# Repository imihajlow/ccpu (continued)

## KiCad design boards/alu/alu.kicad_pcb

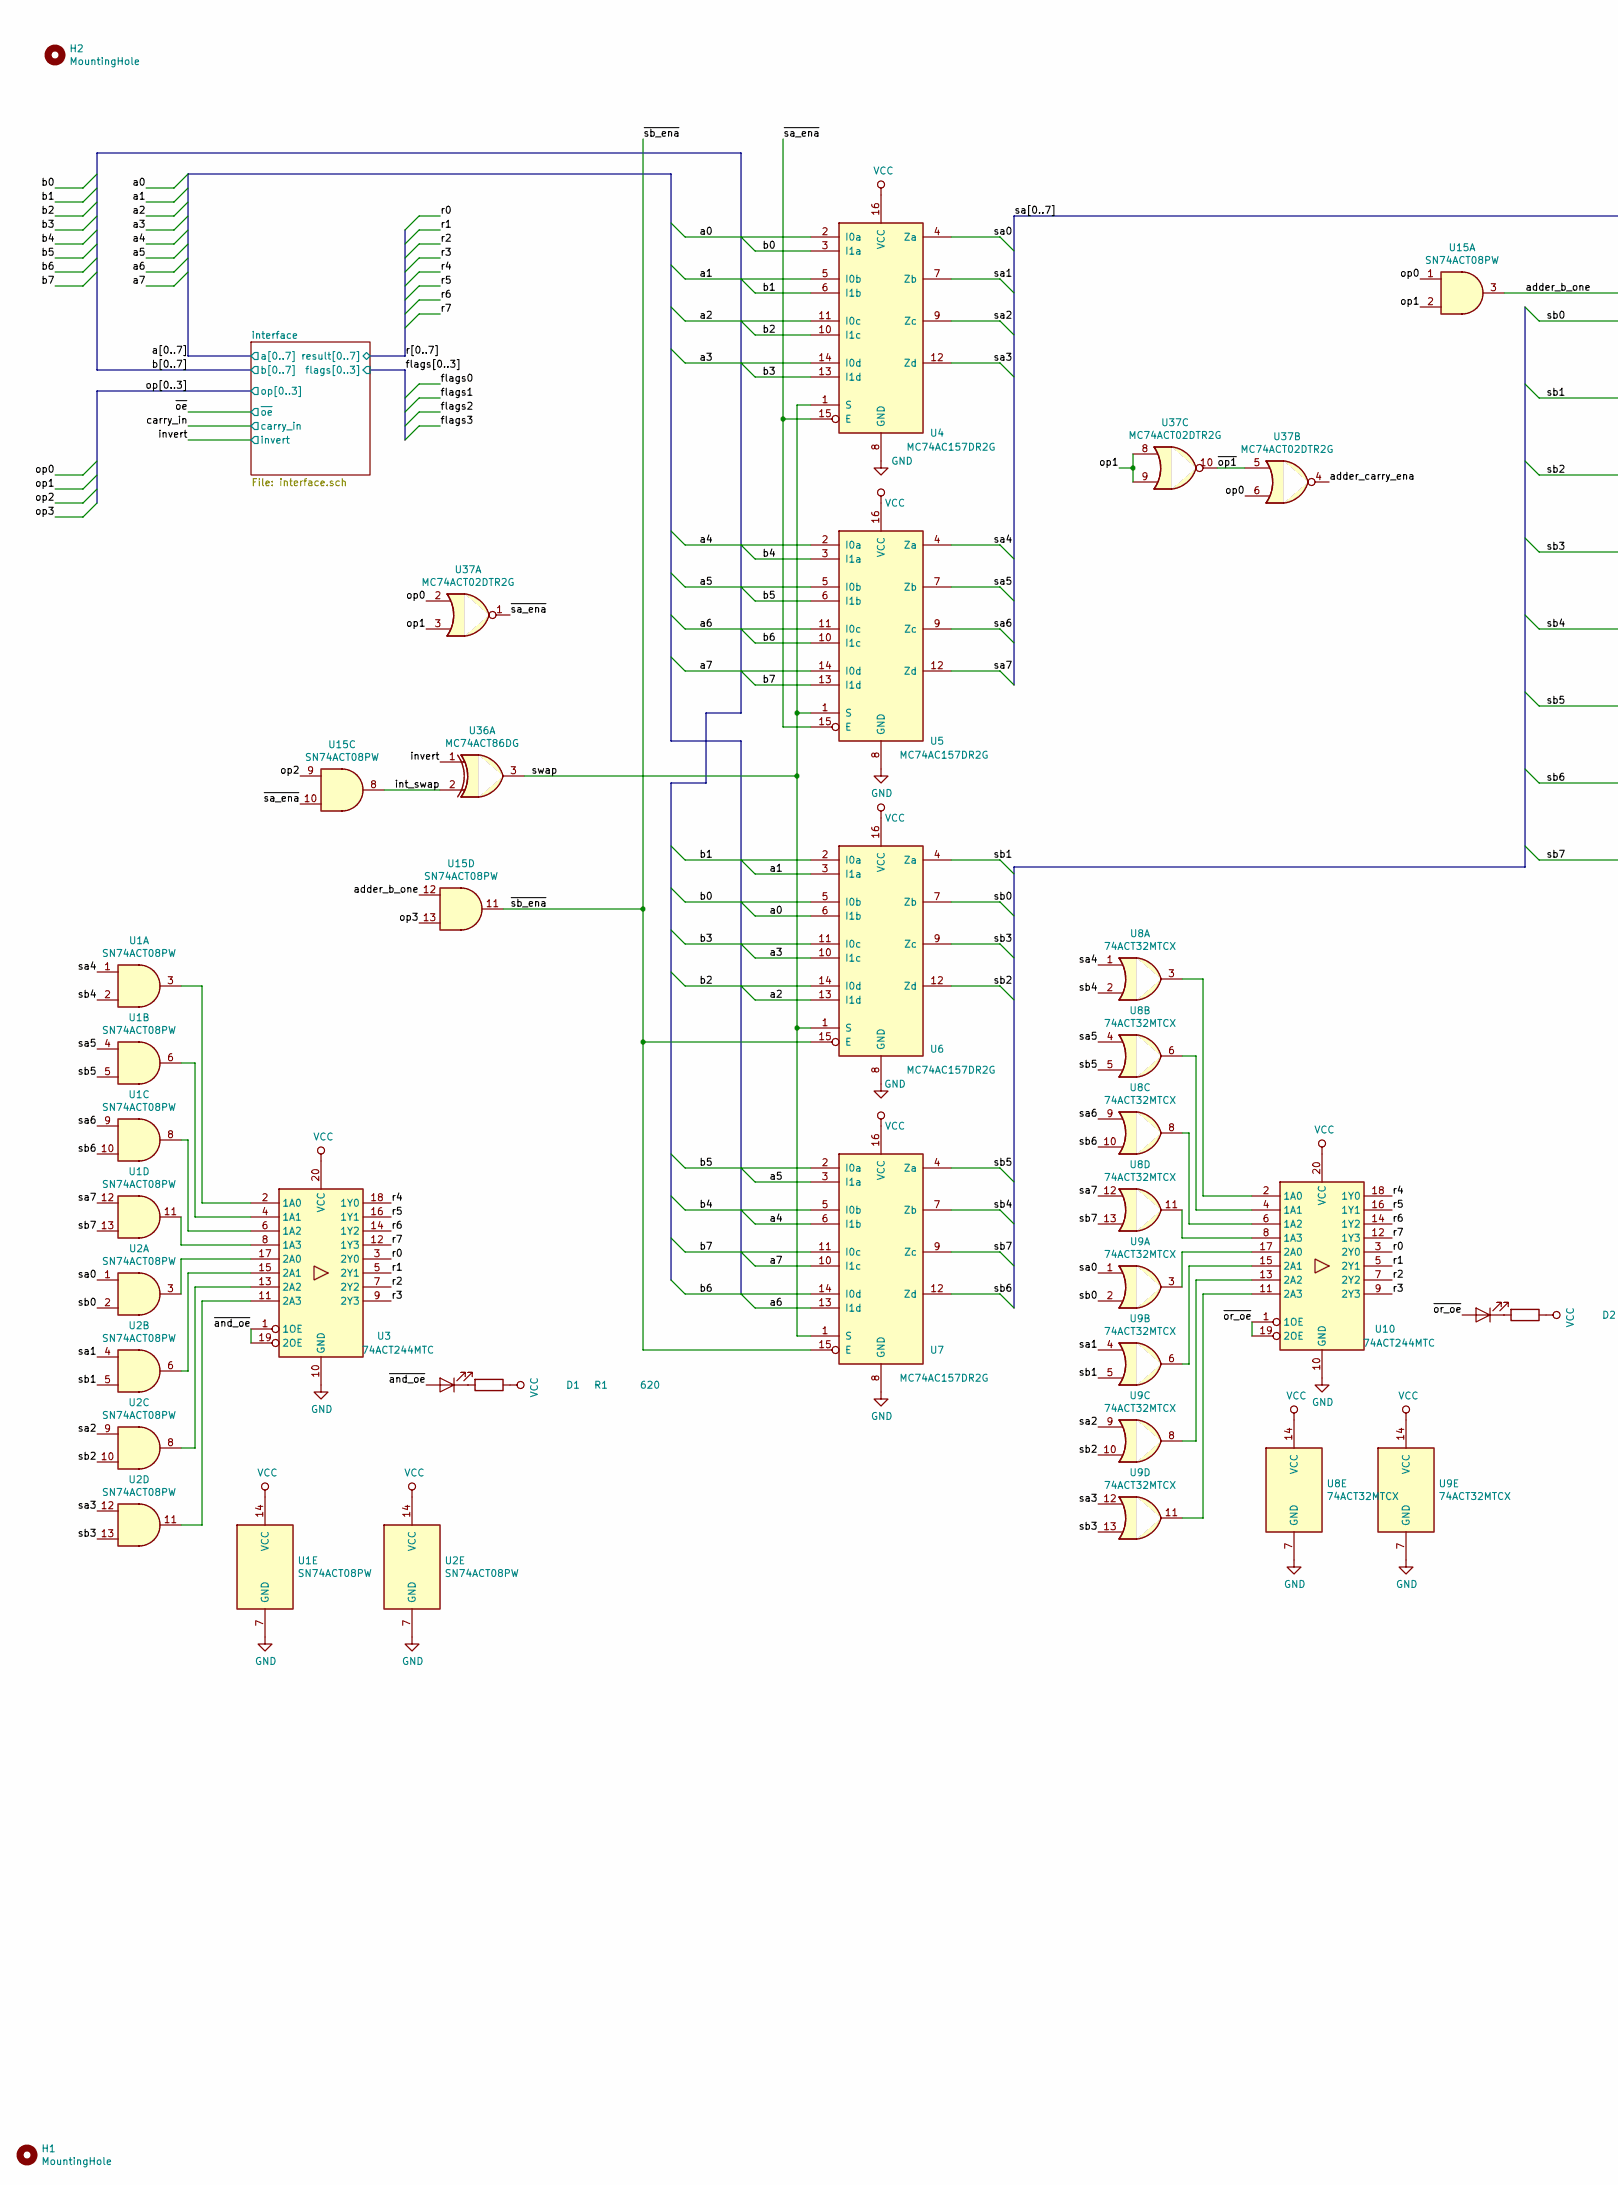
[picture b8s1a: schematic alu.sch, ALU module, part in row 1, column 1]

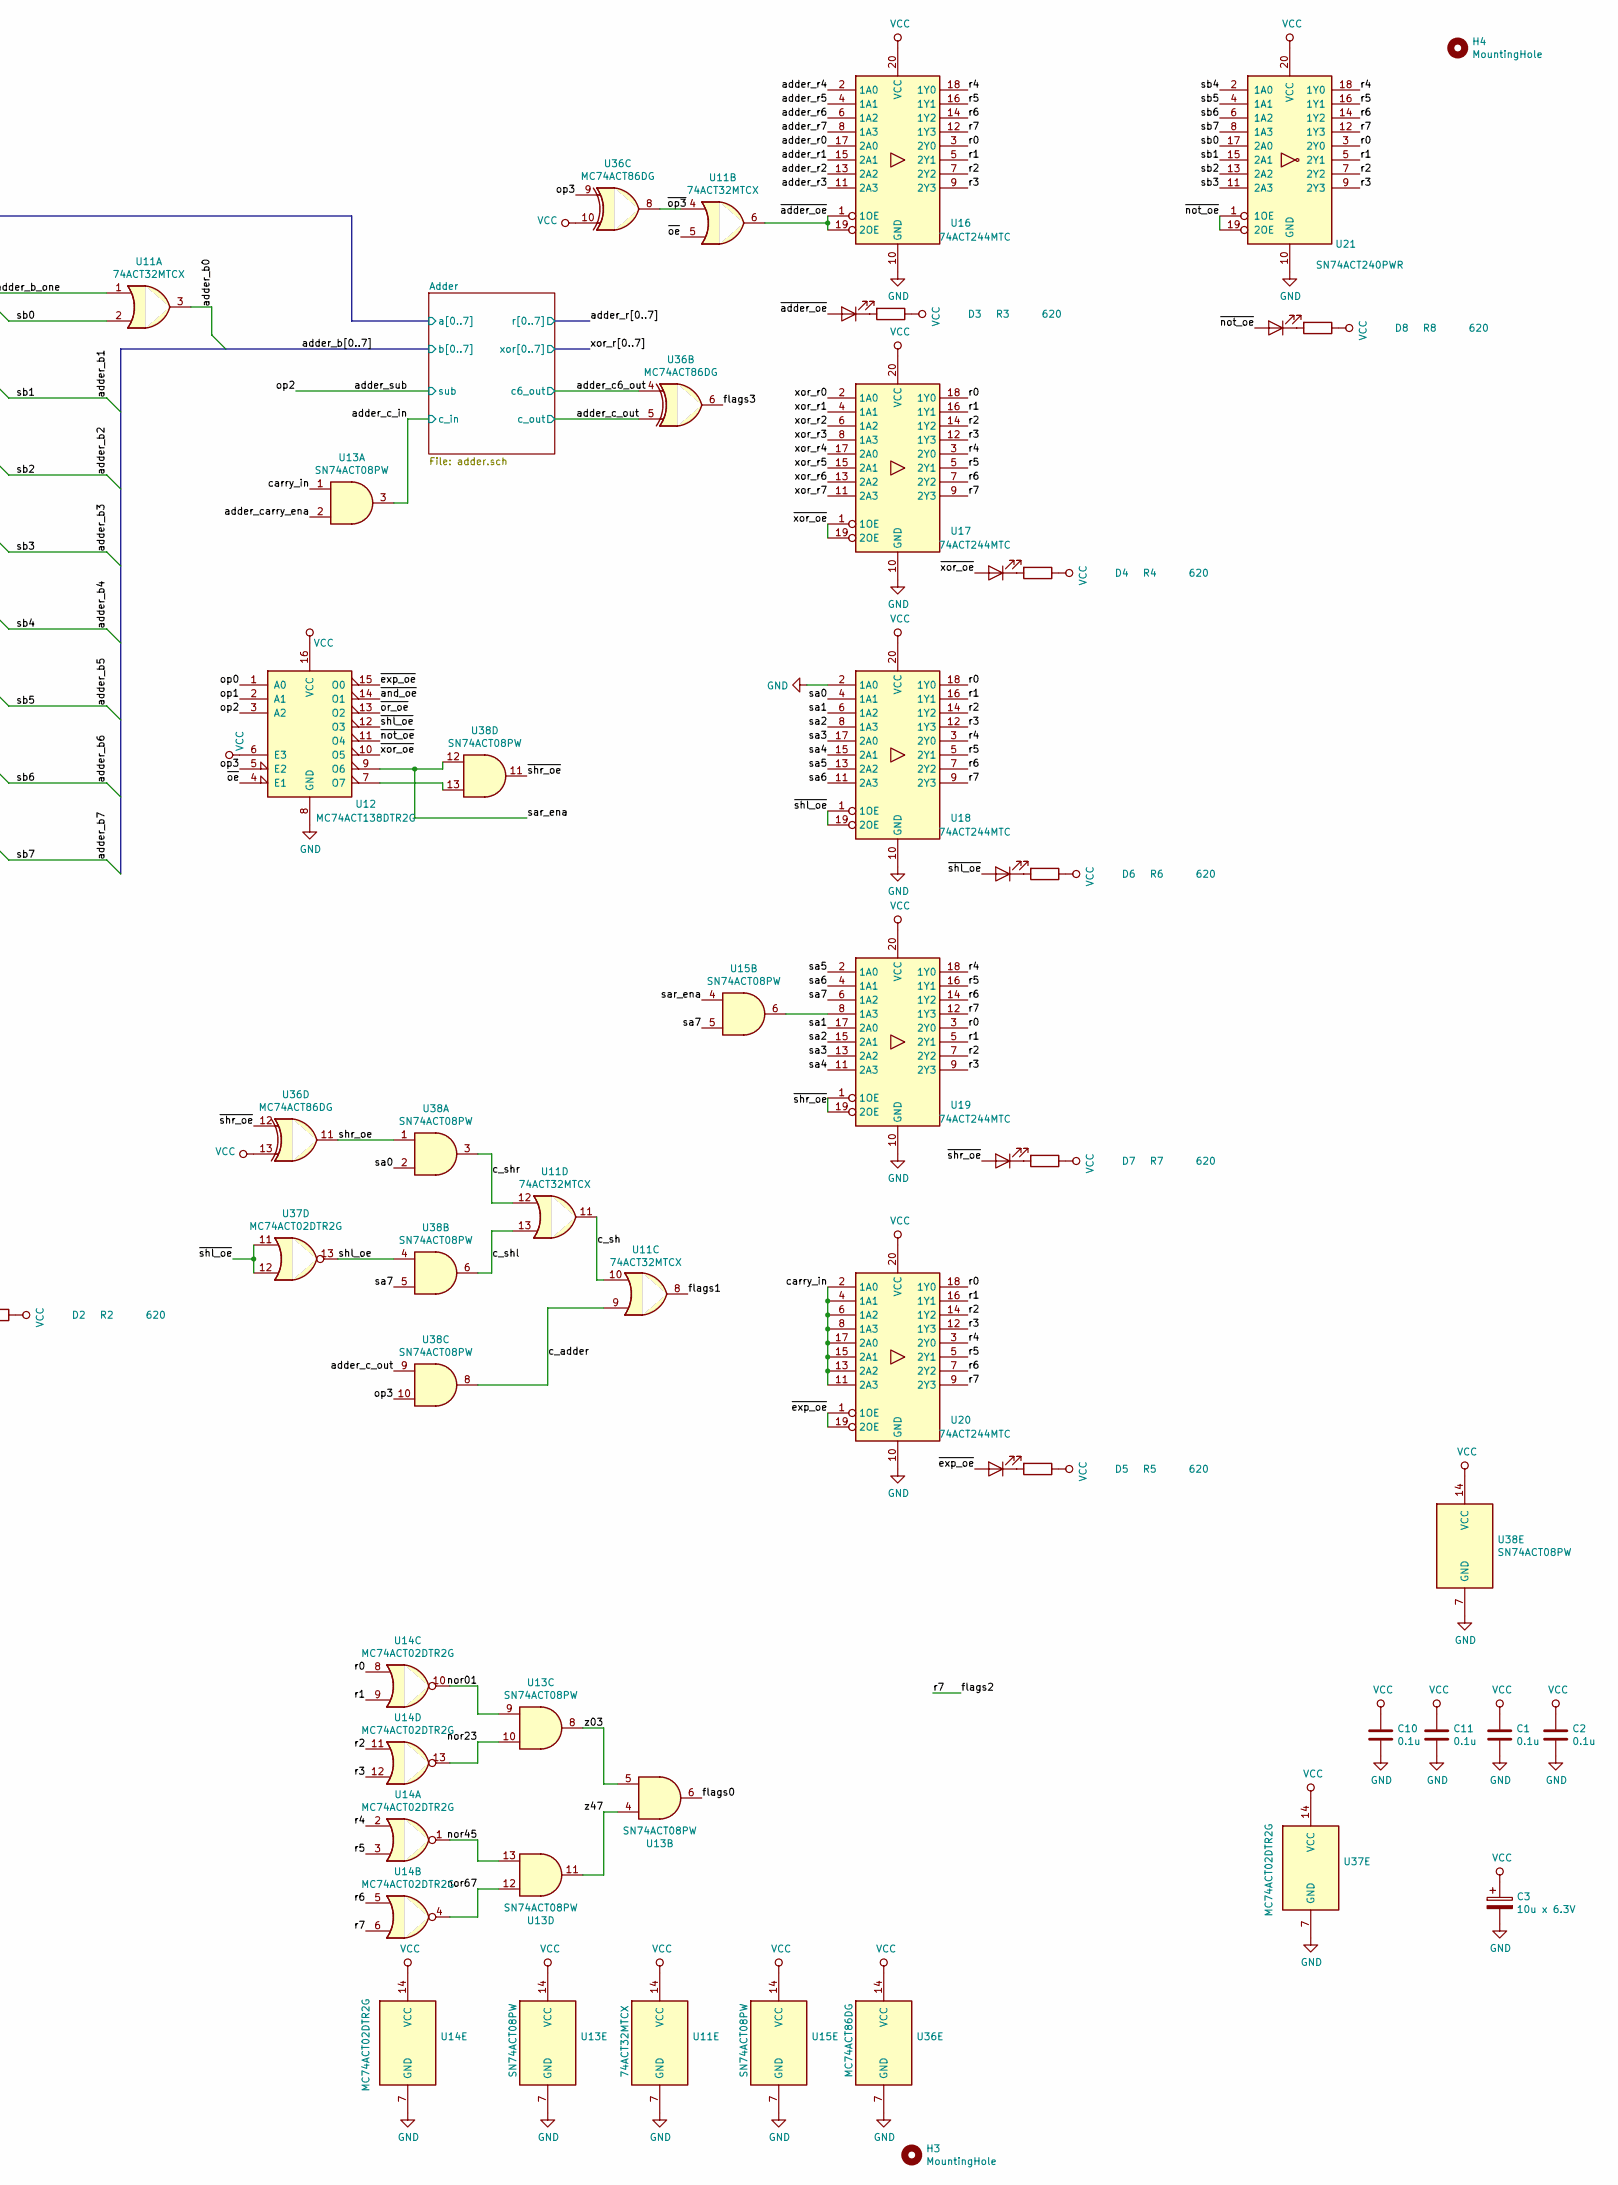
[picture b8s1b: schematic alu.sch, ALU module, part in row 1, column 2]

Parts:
C1, C2, C10, C11: 0.1u; C_0805_2012Metric
C3: 10u x 6.3V; CP_EIA-3528-21_Kemet-B_Pad1.50x2.35mm_HandSolder
D1, D2, D3, D4, D5, D6, D7, D8: KP-2012EC; LED_0805_2012Metric
H1, H2, H3, H4: MountingHole; MountingHole_3.2mm_M3
R1, R2, R3, R4, R5, R6, R7, R8: 620; R_0805_2012Metric
U1, U2, U13, U15, U38: SN74ACT08PW; TSSOP-14_4.4x5mm_P0.65mm
U3, U10, U16, U17, U18, U19, U20: 74ACT244MTC; TSSOP-20_4.4x6.5mm_P0.65mm
U4, U5, U6, U7: MC74AC157DR2G; SOIC-16_3.9x9.9mm_P1.27mm
U8, U9, U11: 74ACT32MTCX; TSSOP-14_4.4x5mm_P0.65mm
U12: MC74ACT138DTR2G; TSSOP-16_4.4x5mm_P0.65mm
U14, U37: MC74ACT02DTR2G; TSSOP-14_4.4x5mm_P0.65mm
U21: SN74ACT240PWR; TSSOP-20_4.4x6.5mm_P0.65mm
U36: MC74ACT86DG; SOIC-14_3.9x8.7mm_P1.27mm

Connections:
/a0: U4.2 (I0a), U6.6 (I1b); also elsewhere on the board
/a1: U4.5 (I0b), U6.3 (I1a); also elsewhere on the board
/a2: U4.11 (I0c), U6.13 (I1d); also elsewhere on the board
/a3: U4.14 (I0d), U6.10 (I1c); also elsewhere on the board
/a4: U5.2 (I0a), U7.6 (I1b); also elsewhere on the board
/a5: U5.5 (I0b), U7.3 (I1a); also elsewhere on the board
/a6: U5.11 (I0c), U7.13 (I1d); also elsewhere on the board
/a7: U5.14 (I0d), U7.10 (I1c); also elsewhere on the board
/adder_b0: U11.3; also elsewhere on the board
/adder_b1: U2.5, U6.4 (Za), U9.5, U21.15 (2A1); also elsewhere on the board
/adder_b2: U2.10, U6.12 (Zd), U9.10, U21.13 (2A2); also elsewhere on the board
/adder_b3: U2.13, U6.9 (Zc), U9.13, U21.11 (2A3); also elsewhere on the board
/adder_b4: U1.2, U7.7 (Zb), U8.2, U21.2 (1A0); also elsewhere on the board
/adder_b5: U1.5, U7.4 (Za), U8.5, U21.4 (1A1); also elsewhere on the board
/adder_b6: U1.10, U7.12 (Zd), U8.10, U21.6 (1A2); also elsewhere on the board
/adder_b7: U1.13, U7.9 (Zc), U8.13, U21.8 (1A3); also elsewhere on the board
/adder_b_one: U11.1, U15.3, U15.12
/adder_c6_out: U36.4; also elsewhere on the board
/adder_c_in: U13.3; also elsewhere on the board
/adder_c_out: U36.5, U38.9; also elsewhere on the board
/adder_carry_ena: U13.2, U37.4
/adder_r0: U16.17 (2A0); also elsewhere on the board
/adder_r1: U16.15 (2A1); also elsewhere on the board
/adder_r2: U16.13 (2A2); also elsewhere on the board
/adder_r3: U16.11 (2A3); also elsewhere on the board
/adder_r4: U16.2 (1A0); also elsewhere on the board
/adder_r5: U16.4 (1A1); also elsewhere on the board
/adder_r6: U16.6 (1A2); also elsewhere on the board
/adder_r7: U16.8 (1A3); also elsewhere on the board
/adder_sub: U12.3 (A2), U15.9; also elsewhere on the board
/b0: U4.3 (I1a), U6.5 (I0b); also elsewhere on the board
/b1: U4.6 (I1b), U6.2 (I0a); also elsewhere on the board
/b2: U4.10 (I1c), U6.14 (I0d); also elsewhere on the board
/b3: U4.13 (I1d), U6.11 (I0c); also elsewhere on the board
/b4: U5.3 (I1a), U7.5 (I0b); also elsewhere on the board
/b5: U5.6 (I1b), U7.2 (I0a); also elsewhere on the board
/b6: U5.10 (I1c), U7.14 (I0d); also elsewhere on the board
/b7: U5.13 (I1d), U7.11 (I0c); also elsewhere on the board
/c_adder: U11.9, U38.8
/c_sh: U11.10, U11.11
/c_shl: U11.13, U38.6
/c_shr: U11.12, U38.3
/carry_in: U13.1, U20.2 (1A0), U20.4 (1A1), U20.6 (1A2), U20.8 (1A3), U20.11 (2A3), U20.13 (2A2), U20.15 (2A1), U20.17 (2A0); also elsewhere on the board
/flags0: U13.6; also elsewhere on the board
/flags1: U11.8; also elsewhere on the board
/flags3: U36.6; also elsewhere on the board
/int_swap: U15.8, U36.2
/invert: U36.1; also elsewhere on the board
/nor01: U13.9, U14.10
/nor23: U13.10, U14.13
/nor45: U13.13, U14.1
/nor67: U13.12, U14.4
/op0: U12.1 (A0), U15.1, U37.2, U37.6; also elsewhere on the board
/op1: U12.2 (A1), U15.2, U37.3, U37.8, U37.9; also elsewhere on the board
/op3: U12.5 (E2), U15.13, U36.9, U38.10; also elsewhere on the board
/r0: U3.3 (2Y0), U10.3 (2Y0), U14.8, U16.3 (2Y0), U17.18 (1Y0), U18.18 (1Y0), U19.3 (2Y0), U20.18 (1Y0), U21.3 (2Y0); also elsewhere on the board
/r1: U3.5 (2Y1), U10.5 (2Y1), U14.9, U16.5 (2Y1), U17.16 (1Y1), U18.16 (1Y1), U19.5 (2Y1), U20.16 (1Y1), U21.5 (2Y1); also elsewhere on the board
/r2: U3.7 (2Y2), U10.7 (2Y2), U14.11, U16.7 (2Y2), U17.14 (1Y2), U18.14 (1Y2), U19.7 (2Y2), U20.14 (1Y2), U21.7 (2Y2); also elsewhere on the board
/r3: U3.9 (2Y3), U10.9 (2Y3), U14.12, U16.9 (2Y3), U17.12 (1Y3), U18.12 (1Y3), U19.9 (2Y3), U20.12 (1Y3), U21.9 (2Y3); also elsewhere on the board
/r4: U3.18 (1Y0), U10.18 (1Y0), U14.2, U16.18 (1Y0), U17.3 (2Y0), U18.3 (2Y0), U19.18 (1Y0), U20.3 (2Y0), U21.18 (1Y0); also elsewhere on the board
/r5: U3.16 (1Y1), U10.16 (1Y1), U14.3, U16.16 (1Y1), U17.5 (2Y1), U18.5 (2Y1), U19.16 (1Y1), U20.5 (2Y1), U21.16 (1Y1); also elsewhere on the board
/r6: U3.14 (1Y2), U10.14 (1Y2), U14.5, U16.14 (1Y2), U17.7 (2Y2), U18.7 (2Y2), U19.14 (1Y2), U20.7 (2Y2), U21.14 (1Y2); also elsewhere on the board
/sa0: U2.1, U4.4 (Za), U9.1, U18.4 (1A1), U38.2; also elsewhere on the board
/sa1: U2.4, U4.7 (Zb), U9.4, U18.6 (1A2), U19.17 (2A0); also elsewhere on the board
/sa2: U2.9, U4.9 (Zc), U9.9, U18.8 (1A3), U19.15 (2A1); also elsewhere on the board
/sa3: U2.12, U4.12 (Zd), U9.12, U18.17 (2A0), U19.13 (2A2); also elsewhere on the board
/sa4: U1.1, U5.4 (Za), U8.1, U18.15 (2A1), U19.11 (2A3); also elsewhere on the board
/sa5: U1.4, U5.7 (Zb), U8.4, U18.13 (2A2), U19.2 (1A0); also elsewhere on the board
/sa6: U1.9, U5.9 (Zc), U8.9, U18.11 (2A3), U19.4 (1A1); also elsewhere on the board
/sa7: U1.12, U5.12 (Zd), U8.12, U15.5, U19.6 (1A2), U38.5; also elsewhere on the board
/sar_ena: U12.9 (O6), U15.4, U38.12
/sb0: U2.2, U6.7 (Zb), U9.2, U11.2, U21.17 (2A0)
/shl_oe: U37.13, U38.4
/shr_oe: U36.11, U38.1
/swap: U4.1 (S), U5.1 (S), U6.1 (S), U7.1 (S), U36.3
/xor_r0: U17.2 (1A0); also elsewhere on the board
/xor_r1: U17.4 (1A1); also elsewhere on the board
/xor_r2: U17.6 (1A2); also elsewhere on the board
/xor_r3: U17.8 (1A3); also elsewhere on the board
/xor_r4: U17.17 (2A0); also elsewhere on the board
/xor_r5: U17.15 (2A1); also elsewhere on the board
/xor_r6: U17.13 (2A2); also elsewhere on the board
/xor_r7: U17.11 (2A3); also elsewhere on the board
/z03: U13.5, U13.8
/z47: U13.4, U13.11
/~adder_oe: D3.2 (A), U11.6, U16.1 (1OE), U16.19 (2OE)
/~and_oe: D1.2 (A), U3.1 (1OE), U3.19 (2OE), U12.14 (O1)
/~exp_oe: D5.2 (A), U12.15 (O0), U20.1 (1OE), U20.19 (2OE)
/~not_oe: D8.2 (A), U12.11 (O4), U21.1 (1OE), U21.19 (2OE)
/~oe: U11.5, U12.4 (E1); also elsewhere on the board
/~op1: U37.5, U37.10
/~op3: U11.4, U36.8
/~or_oe: D2.2 (A), U10.1 (1OE), U10.19 (2OE), U12.13 (O2)
/~sa_ena: U4.15 (E), U5.15 (E), U15.10, U37.1
/~sb_ena: U6.15 (E), U7.15 (E), U15.11
/~shl_oe: D6.2 (A), U12.12 (O3), U18.1 (1OE), U18.19 (2OE), U37.11, U37.12
/~shr_oe: D7.2 (A), U19.1 (1OE), U19.19 (2OE), U36.12, U38.11
/~xor_oe: D4.2 (A), U12.10 (O5), U17.1 (1OE), U17.19 (2OE)
GND: C1.2, C2.2, C3.2, C10.2, C11.2, U1.7 (GND), U2.7 (GND), U3.10 (GND), U4.8 (GND), U5.8 (GND), U6.8 (GND), U7.8 (GND), U8.7 (GND), U9.7 (GND), U10.10 (GND), U11.7 (GND), U12.8 (GND), U13.7 (GND), U14.7 (GND), U15.7 (GND), U16.10 (GND), U17.10 (GND), U18.2 (1A0), U18.10 (GND), U19.10 (GND), U20.10 (GND), U21.10 (GND), U36.7 (GND), U37.7 (GND), U38.7 (GND); also elsewhere on the board
unnamed: D1.1 (K), R1.2
unnamed: D2.1 (K), R2.2
unnamed: D3.1 (K), R3.2
unnamed: D4.1 (K), R4.2
unnamed: D5.1 (K), R5.2
unnamed: D6.1 (K), R6.2
unnamed: D7.1 (K), R7.2
unnamed: D8.1 (K), R8.2
unnamed: U1.3, U3.2 (1A0)
unnamed: U1.6, U3.4 (1A1)
unnamed: U1.8, U3.6 (1A2)
unnamed: U1.11, U3.8 (1A3)
unnamed: U2.3, U3.17 (2A0)
unnamed: U2.6, U3.15 (2A1)
unnamed: U2.8, U3.13 (2A2)
unnamed: U2.11, U3.11 (2A3)
unnamed: U8.3, U10.2 (1A0)
unnamed: U8.6, U10.4 (1A1)
unnamed: U8.8, U10.6 (1A2)
unnamed: U8.11, U10.8 (1A3)
unnamed: U9.11, U10.11 (2A3)
unnamed: U9.8, U10.13 (2A2)
unnamed: U9.6, U10.15 (2A1)
unnamed: U9.3, U10.17 (2A0)
unnamed: U12.7 (O7), U38.13
unnamed: U15.6, U19.8 (1A3)
VCC: C1.1, C2.1, C3.1, C10.1, C11.1, R1.1, R2.1, R3.1, R4.1, R5.1, R6.1, R7.1, R8.1, U1.14 (VCC), U2.14 (VCC), U3.20 (VCC), U4.16 (VCC), U5.16 (VCC), U6.16 (VCC), U7.16 (VCC), U8.14 (VCC), U9.14 (VCC), U10.20 (VCC), U11.14 (VCC), U12.6 (E3), U12.16 (VCC), U13.14 (VCC), U14.14 (VCC), U15.14 (VCC), U16.20 (VCC), U17.20 (VCC), U18.20 (VCC), U19.20 (VCC), U20.20 (VCC), U21.20 (VCC), U36.10, U36.13, U36.14 (VCC), U37.14 (VCC), U38.14 (VCC); also elsewhere on the board

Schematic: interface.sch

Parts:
J1: 61304021021; PinHeader_2x20_P2.54mm_Horizontal

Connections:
/a0: J1.19; also elsewhere on the board
/a1: J1.20; also elsewhere on the board
/a2: J1.21; also elsewhere on the board
/a3: J1.22; also elsewhere on the board
/a4: J1.23; also elsewhere on the board
/a5: J1.24; also elsewhere on the board
/a6: J1.25; also elsewhere on the board
/a7: J1.26; also elsewhere on the board
/adder_sub: J1.29; also elsewhere on the board
/b0: J1.3; also elsewhere on the board
/b1: J1.5; also elsewhere on the board
/b2: J1.7; also elsewhere on the board
/b3: J1.9; also elsewhere on the board
/b4: J1.4; also elsewhere on the board
/b5: J1.6; also elsewhere on the board
/b6: J1.8; also elsewhere on the board
/b7: J1.10; also elsewhere on the board
/carry_in: J1.33; also elsewhere on the board
/flags0: J1.35; also elsewhere on the board
/flags1: J1.36; also elsewhere on the board
/flags3: J1.38; also elsewhere on the board
/invert: J1.31; also elsewhere on the board
/op0: J1.27; also elsewhere on the board
/op1: J1.28; also elsewhere on the board
/op3: J1.30; also elsewhere on the board
/r0: J1.11; also elsewhere on the board
/r1: J1.12; also elsewhere on the board
/r2: J1.13; also elsewhere on the board
/r3: J1.14; also elsewhere on the board
/r4: J1.15; also elsewhere on the board
/r5: J1.16; also elsewhere on the board
/r6: J1.17; also elsewhere on the board
/~oe: J1.32; also elsewhere on the board
GND: J1.2, J1.39; also elsewhere on the board
VCC: J1.1, J1.40; also elsewhere on the board

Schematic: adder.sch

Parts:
C4, C5, C6, C7, C8, C9: 0.1u; C_0805_2012Metric
U22, U23, U24, U25, U26, U27, U28, U29: MC74ACT86DG; SOIC-14_3.9x8.7mm_P1.27mm
U30, U31, U32, U33: SN74ACT08PW; TSSOP-14_4.4x5mm_P0.65mm
U34, U35: 74ACT32MTCX; TSSOP-14_4.4x5mm_P0.65mm

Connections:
/adder_b0: U22.2, U30.1; also elsewhere on the board
/adder_b1: U23.2, U30.12; also elsewhere on the board
/adder_b2: U24.2, U31.1; also elsewhere on the board
/adder_b3: U25.2, U31.12; also elsewhere on the board
/adder_b4: U26.2, U32.1; also elsewhere on the board
/adder_b5: U27.2, U32.12; also elsewhere on the board
/adder_b6: U28.2, U33.1; also elsewhere on the board
/adder_b7: U29.2, U33.12; also elsewhere on the board
/adder_c6_out: U29.5, U33.9, U35.8; also elsewhere on the board
/adder_c_in: U22.5, U30.4; also elsewhere on the board
/adder_c_out: U35.11; also elsewhere on the board
/adder_r0: U22.6; also elsewhere on the board
/adder_r1: U23.6; also elsewhere on the board
/adder_r2: U24.6; also elsewhere on the board
/adder_r3: U25.6; also elsewhere on the board
/adder_r4: U26.6; also elsewhere on the board
/adder_r5: U27.6; also elsewhere on the board
/adder_r6: U28.6; also elsewhere on the board
/adder_r7: U29.6; also elsewhere on the board
/adder_sub: U22.10, U22.13, U23.10, U23.13, U24.10, U24.13, U25.10, U25.13, U26.10, U26.13, U27.10, U27.13, U28.10, U28.13, U29.10, U29.13; also elsewhere on the board
/sa0: U22.1, U22.12; also elsewhere on the board
/sa1: U23.1, U23.12; also elsewhere on the board
/sa2: U24.1, U24.12; also elsewhere on the board
/sa3: U25.1, U25.12; also elsewhere on the board
/sa4: U26.1, U26.12; also elsewhere on the board
/sa5: U27.1, U27.12; also elsewhere on the board
/sa6: U28.1, U28.12; also elsewhere on the board
/sa7: U29.1, U29.12; also elsewhere on the board
/xor_r0: U22.3, U22.4, U22.9; also elsewhere on the board
/xor_r1: U23.3, U23.4, U23.9; also elsewhere on the board
/xor_r2: U24.3, U24.4, U24.9; also elsewhere on the board
/xor_r3: U25.3, U25.4, U25.9; also elsewhere on the board
/xor_r4: U26.3, U26.4, U26.9; also elsewhere on the board
/xor_r5: U27.3, U27.4, U27.9; also elsewhere on the board
/xor_r6: U28.3, U28.4, U28.9; also elsewhere on the board
/xor_r7: U29.3, U29.4, U29.9; also elsewhere on the board
GND: C4.2, C5.2, C6.2, C7.2, C8.2, C9.2, U22.7 (GND), U23.7 (GND), U24.7 (GND), U25.7 (GND), U26.7 (GND), U27.7 (GND), U28.7 (GND), U29.7 (GND), U30.7 (GND), U31.7 (GND), U32.7 (GND), U33.7 (GND), U34.7 (GND), U35.7 (GND); also elsewhere on the board
unnamed: U22.8, U30.5
unnamed: U22.11, U30.2
unnamed: U23.5, U30.9, U34.3
unnamed: U23.8, U30.10
unnamed: U23.11, U30.13
unnamed: U24.5, U31.4, U34.6
unnamed: U24.8, U31.5
unnamed: U24.11, U31.2
unnamed: U25.5, U31.9, U34.8
unnamed: U25.8, U31.10
unnamed: U25.11, U31.13
unnamed: U26.5, U32.4, U34.11
unnamed: U26.8, U32.5
unnamed: U26.11, U32.2
unnamed: U27.5, U32.9, U35.3
unnamed: U27.8, U32.10
unnamed: U27.11, U32.13
unnamed: U28.5, U33.4, U35.6
unnamed: U28.8, U33.5
unnamed: U28.11, U33.2
unnamed: U29.8, U33.10
unnamed: U29.11, U33.13
unnamed: U30.3, U34.2
unnamed: U30.6, U34.1
unnamed: U30.8, U34.4
unnamed: U30.11, U34.5
unnamed: U31.3, U34.10
unnamed: U31.6, U34.9
unnamed: U31.8, U34.12
unnamed: U31.11, U34.13
unnamed: U32.3, U35.2
unnamed: U32.6, U35.1
unnamed: U32.8, U35.4
unnamed: U32.11, U35.5
unnamed: U33.3, U35.10
unnamed: U33.6, U35.9
unnamed: U33.8, U35.12
unnamed: U33.11, U35.13
VCC: C4.1, C5.1, C6.1, C7.1, C8.1, C9.1, U22.14 (VCC), U23.14 (VCC), U24.14 (VCC), U25.14 (VCC), U26.14 (VCC), U27.14 (VCC), U28.14 (VCC), U29.14 (VCC), U30.14 (VCC), U31.14 (VCC), U32.14 (VCC), U33.14 (VCC), U34.14 (VCC), U35.14 (VCC); also elsewhere on the board

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
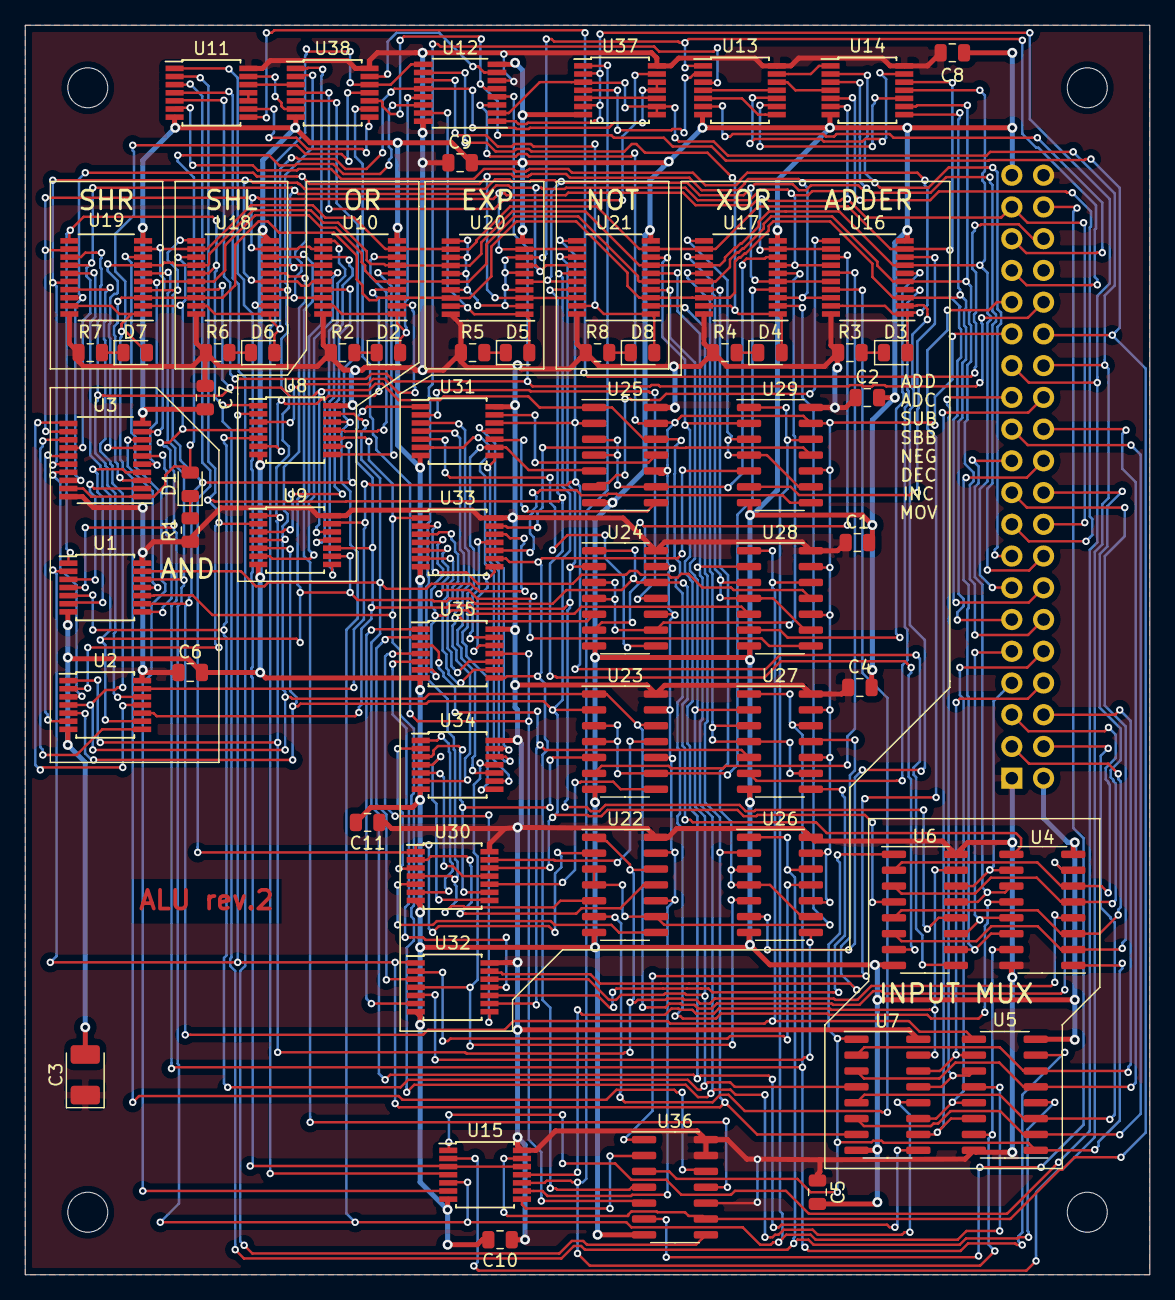
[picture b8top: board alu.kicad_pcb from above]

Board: 2 copper layers, 90.0 x 100.0 mm, 70 parts (1 on the bottom side), 165 nets.

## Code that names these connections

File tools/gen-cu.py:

#!/usr/bin/env python3
bits = 15

def encode_address(ir, clk, condition_result, n_mem_rdy, cycle, s1, s2, a14):
    return ir | (clk << 8) | (condition_result << 9) | (n_mem_rdy << 11) | (cycle << 10) | (s1 << 12) | (s2 << 13) | (a14 << 14)

def encode_a(n_oe_mem, n_we_mem, n_oe_d_di, inc_ip, addr_dp, we_ir):
    return n_oe_mem | (n_we_mem << 1) | (n_oe_d_di << 2) | (inc_ip << 3) | (addr_dp << 4) | (we_ir << 5)

def encode_b(n_oe_pl_alu, n_oe_ph_alu, n_oe_b_alu, n_oe_a_d, n_oe_b_d, n_we_flags, s1_d, s2_d):
    return n_oe_pl_alu | (n_oe_ph_alu << 1) | (n_oe_b_alu << 2) | (n_oe_a_d << 3) | (n_oe_b_d << 4) | (n_we_flags << 5) | (s1_d << 6) | (s2_d << 7)

def encode_c(n_oe_alu_di, n_reset_cycle, swap_p, n_we_pl, n_we_ph, we_a, we_b):
    return n_oe_alu_di | (n_reset_cycle << 1) | (swap_p << 2) | (n_we_pl << 3) | (n_we_ph << 4) | (we_a << 5) | (we_b << 6)

def write_hex(filename, array):
    with open(filename, "w") as f:
        for i,x in enumerate(array):
            f.write("{:02x}".format(x))
            if (i & 0xf) == 0xf:
                f.write("\n")
            else:
                f.write(" ")

def write_bin(filename, array):
    with open(filename, "wb") as f:
        ba = bytearray(array)
        f.write(ba)

def set_oe_alu(ir, r):
    n = ir & 0x03
    key = ["n_oe_zero_alu", "n_oe_b_alu", "n_oe_pl_alu", "n_oe_ph_alu"][n]
    r[key] = 0

def set_we(ir, r):
    n = ir & 0x03
    key = ["we_a", "we_b", "n_we_pl", "n_we_ph"][n]
    if n < 2:
        r[key] = 1 # active high
    else:
        r[key] = 0 # active low

def set_oe_x_d(ir, r):
    n = ir & 0x01
    key = ["n_oe_a_d", "n_oe_b_d"][n]
    r[key] = 0

def get(ir, clk, condition_result, n_mem_rdy, cycle):
    r = {
        "n_oe_mem": 0,
        "n_we_mem": 1,
        "n_oe_d_di": 1,
        "inc_ip": 1,
        "addr_dp": 0,
        "n_we_pl": 1,
        "n_we_ph": 1,
        "we_a": 0,
        "we_b": 0,
        "n_oe_pl_alu": 1,
        "n_oe_ph_alu": 1,
        "n_oe_b_alu": 1,
        "n_oe_zero_alu": 1,
        "n_oe_a_d": 1,
        "n_oe_b_d": 1,
        "n_we_flags": 1,
        "n_oe_alu_di": 1,
        "n_reset_cycle": 0,
        "swap_p": 0,
        "we_ir": 1
    }

    ir_is_alu = (ir & 0x80) == 0
    ir_is_jmp = (ir & 0xc0) == 0xc0
    ir_is_2cy = (ir & 0xa0) == 0xa0
    ir_is_sto = (ir & 0x90) == 0x90

    ld = (ir & 0xf0) == 0x80
    st = (ir & 0xf0) == 0xb0
    alu = (ir & 0x80) == 0
    ldi = (ir & 0xf0) == 0xa0
    jc = (ir & 0xf0) == 0xc0

    if ir & 0x80 == 0:
        # ALU operation
        # 0oooordd
        op = ir >> 3
        inverse = ir & 0x04 != 0
        if op != 0x08: # MOV
            r["n_we_flags"] = 0
        r["n_oe_alu_di"] = 0

        set_oe_alu(ir, r)
        if not inverse:
            r["we_a"] = 1
        else:
            set_we(ir, r)
    elif ir & 0xf0 == 0x80:
        # LD operation
        # 1000__dd
        set_we(ir, r)
        r["n_oe_d_di"] = 0
        if clk:
            r["addr_dp"] = 1
        else:
            r["addr_dp"] = 0
    elif ir & 0xf0 == 0xb0:
        # ST operation
        # 1011___d
        r["n_reset_cycle"] = 1
        if cycle == 0:
            r["n_oe_mem"] = 1
            r["inc_ip"] = 0
            r["addr_dp"] = 1
            if clk == 1:
                r["n_we_mem"] = 1
            else:
                r["n_we_mem"] = 0
                set_oe_x_d(ir, r)
                r["we_ir"] = 0
        else:
            if clk == 1:
                r["we_ir"] = 0
                set_oe_x_d(ir, r)
                r["n_oe_mem"] = 1
                r["addr_dp"] = 1
    elif ir & 0xf0 == 0xa0:
        # LDI operation
        # 1010__dd
        r["n_reset_cycle"] = 1
        if cycle == 0:
            if clk == 0:
                r["we_ir"] = 0
        else:
            r["n_oe_d_di"] = 0
            set_we(ir, r)
            if clk == 1:
                r["we_ir"] = 0
    elif ir & 0xf0 == 0xc0:
        # Jx operation
        # 1010icff
        conditional = ir & 0x08 == 0
        inverse = ir & 0x04 != 0
        success = not conditional or (condition_result != inverse)
        if success:
            r["swap_p"] = 1
    return r

def main():
    part_a = [0] * (2 ** bits)
    part_b = [0] * (2 ** bits)
    part_c = [0] * (2 ** bits)

    for ir in range(256):
        for clk in range(2):
            for condition_result in range(2):
                for n_mem_rdy in range(2):
                    for cycle in range(2):
                        for s1 in range(2):
                            for s2 in range(2):
                                for a14 in range(2):
                                    address = encode_address(ir, clk, condition_result, n_mem_rdy, cycle, s1, s2, a14)
                                    r = get(ir, clk, condition_result, n_mem_rdy, cycle)
                                    part_a[address] = encode_a(r["n_oe_mem"], r["n_we_mem"], r["n_oe_d_di"], r["inc_ip"], r["addr_dp"], r["we_ir"])
                                    part_b[address] = encode_b(r["n_oe_pl_alu"], r["n_oe_ph_alu"], r["n_oe_b_alu"], r["n_oe_a_d"], r["n_oe_b_d"], r["n_we_flags"], 0, 0)
                                    part_c[address] = encode_c(r["n_oe_alu_di"], r["n_reset_cycle"], r["swap_p"], r["n_we_pl"], r["n_we_ph"], r["we_a"], r["we_b"])
    write_hex("cu_a.mem", part_a)
    write_hex("cu_b.mem", part_b)
    write_hex("cu_c.mem", part_c)
    write_bin("cu_a.bin", part_a)
    write_bin("cu_b.bin", part_b)
    write_bin("cu_c.bin", part_c)

if __name__ == '__main__':
    main()

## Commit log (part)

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2020-12-19 IO: refill zones on PCB
2020-12-19 IO: production files rev. 2
2020-12-19 Control: production files rev. 3
2020-12-19 VGA: production files rev. 1
2020-12-30 A less ugly font
2021-01-02 Memory check for the new IO board
2021-01-02 Linker: segments which can be copied from ROM to RAM
2021-01-02 IO: errata
2021-01-03 VGA calibration document
2021-01-03 Natrix: fix small bug
2021-01-03 VGA test program
2021-01-06 VGA errata
2021-01-06 Generate whole font ROM
2021-01-06 VGA library and test program
2021-01-06 Fix English
2021-01-13 Update VGA library and test program to work around a hw bug
2021-01-13 Quasipixel library and pixel drawing program
2021-01-13 Conway's game of life implementation
2021-01-14 Natrix: allow shifts between constants of different type
2021-01-16 Natrix: pointer subtraction
2021-01-16 Natrix: for loops
2021-01-16 Simple VGA maze game
2021-01-16 Natrix: syntax error reporting
2021-01-16 Natrix: fix error message format
2021-01-17 Maze: ugly line of sight algorithm
2021-01-17 Simulator: VGA
2021-01-18 Registers: change IR clock phase
2021-01-18 Registers: more decoupling capacitors
2021-01-18 Registers: change logic family to HC and LV-A
2021-01-18 Registers: new board started
2021-01-21 Registers board rev. 2
    Implement RDY mechanism by suspending clock signal
    Take caution against crosstalk on sensitive line
    Add proper decoupling capacitors
2021-01-21 IO board rev. 3
    Move side connectors
    Take caution against crosstalk
2021-01-21 IO: change logic family
2021-01-21 Registers: update text
2021-01-21 IO: production files rev. 3
2021-01-22 Registers: add a pull-up on RDY
2021-01-22 Registers: update production files
2021-01-24 Maze: hide far away tiles
2021-01-25 Registers: update PCB text
2021-01-25 IO: remove B_SilkS production file
2021-01-27 Natrix: handle VisitorError
2021-01-27 Natrix: delete case handled by sugar transformer
2021-01-27 Natrix: resolve variable names in a tree transformer
2021-01-27 Natrix: rename visitors
2021-01-27 Natrix: delete duplicated functionality
2021-01-27 Natrix: dereferenced struct member write access
2021-01-27 Natrix: struct syntax
2021-01-27 Natrix: struct member address
2021-01-27 Natrix: simple struct member write access
2021-01-27 Natrix: alignment WIP
2021-01-27 Linker: support different memory layouts
2021-01-27 Natrix: struct member access by tree transform
2021-01-27 Natrix: struct unit tests
2021-01-30 Natrix: sizeof expression
2021-01-30 Natrix: update TODO and README
2021-01-30 Natrix: the arrow operator
2021-01-31 Natrix: aligned structs when all fields are aligned
2021-01-31 Natrix: copy struct
2021-01-31 Natrix: copy structs, handle arrays inside structs
2021-02-06 VGA: delete RDY workaround
2021-02-06 Faster vga_clear
2021-02-06 SPI timing diagram
2021-02-06 Indent with spaces
2021-02-06 Vario: schematic started
2021-02-06 PS/2: better test bench
2021-02-06 PS/2 schematic
2021-02-06 PS/2: send and receive draft
2021-02-06 PS/2: accurately simulate input
2021-02-06 Automatic waveform rendering
2021-02-06 PS/2: keep the recv register intact when data is there
2021-02-06 PS/2: 74280 parity checker
2021-02-06 PS/2: decoupling capacitors
2021-02-06 SPI: some capacitors
2021-02-06 Vario: memory card connection and power
2021-02-06 SPI: implement missing logic
2021-02-07 VGA stripes program
2021-02-07 SPI: invert RDY
2021-02-07 Add interface documentaion
2021-02-07 Natrix: declare global struct variables
2021-02-08 PS/2: different select signals
2021-02-08 Vario: address selection
2021-02-08 Vario: status LEDs
2021-02-08 Vario: transistors and capacitors
2021-02-09 Vario: board started, connectors layout
2021-02-10 Vario: power nets
2021-02-11 Vario: board, delete redundant 7474
2021-02-11 Vario: add dimension
2021-02-12 Vario: move crosstalk-sensitive traces
2021-02-13 Vario: rectangular pads on the board
2021-02-20 Optimize Life program
2021-02-21 Natrix: proper for loops
2021-02-21 Linker: fit sections smarter, fill holes
2021-02-24 Natrix: support sections when defining functions
2021-02-26 PS/2 test program
2021-02-27 Vario: kikad-rescue
2021-02-27 PS/2 test program update
2021-02-27 Vario: exact RC values
2021-02-27 PS/2 utility library
2021-02-27 Maze and Life with PS/2 keyboard
2021-02-28 Memory card + FAT
2021-03-01 Migrate build system to SCons
2021-03-01 u32: cast
2021-03-01 u32: comparison and some tests
2021-03-02 u32: unsigned comparison
2021-03-02 u32: dereference
2021-03-02 u32: binary
2021-03-02 Natrix: large pointer indexing
2021-03-02 Natrix: large pointer subtraction
2021-03-03 Natrix: large pointer subtraction in place
2021-03-03 u32: shl
2021-03-03 u32: shl in place
2021-03-03 u32: shl by var
2021-03-03 u32: shr by var
2021-03-03 u32: shr by const
2021-03-03 Natrix: remove redundant code
2021-03-03 u32: FAT demo program with u32
2021-03-04 Natrix: put functions in own sections
2021-03-04 Natrix: runtime functions in separate sections
2021-03-04 Natrix: put literals in own sections
2021-03-04 Rename some sections to allow linker optimization
2021-03-04 Reorganize scons script
2021-03-05 More
2021-03-05 PS/2: text typing
2021-03-06 FAT: multiple file descriptors
    Also, fix Natrix bug
2021-03-06 FAT: read subdirectories
2021-03-06 FAT: seek
2021-03-06 FAT: open file by name
2021-03-08 Card: only read whole blocks
2021-03-08 Card: block index, not byte index
2021-03-08 Import tools as python modules when building
2021-03-08 Fileshell app started
2021-03-09 Fileshell: typing a file
2021-03-09 Fileshell: append into file
2021-03-09 VGA: less ugly font
2021-03-10 FAT: faster file search, debug messages
2021-03-10 FAT: better error reporting
2021-03-10 FAT: detect FAT bit size
2021-03-10 Fileshell: fix bug in file viewer
2021-03-12 Linker: list layouts automatically
2021-03-13 Fix linking ramtext sections
2021-03-13 Linker: fix API bug
2021-03-13 Matrix: exit by PS/2 key
2021-03-13 Fileshell: check file size
2021-03-13 Fileshell: load app into lo RAM
2021-03-14 Loadable calc app
2021-03-14 Loadable maze app, jump to any level
2021-03-14 Loadable life app
2021-03-14 Pong game
2021-03-15 Syscall WIP
2021-03-16 Syscall test app
2021-03-16 Rewrite card driver in assembly to save space
2021-03-17 Card: delete extra parameter
2021-03-17 FAT: init and mount as different methods; stale descriptors
2021-03-17 Natrix: section attributes are not allowed for imported vars
2021-03-17 Section for syscalls
2021-03-17 Linker: YAML layout scripts
2021-03-17 Linker: support minimal begin address property of a segment
2021-03-17 Uncomment main.app
2021-03-18 FAT: fix writing empty files
2021-03-18 Fileshell: don't run extensions
2021-03-18 Natrix: introduce Location class instead of string/int
2021-03-18 Natrix: optimize byte operations by storing values in A
2021-03-18 Natrix: fix some missed cases
2021-03-18 Natrix: fix typo
2021-03-20 Simulator: VGA GUI, IPC and stuff
2021-03-20 Simulator: small keyboard as a mem module
2021-03-20 Simulator: PS2 simulator
2021-03-20 Simulator: delete messages
2021-03-20 Simulator: CR and lo RAM
2021-03-21 RSim: minimal simulator in Rust
2021-03-22 RSim: handle ctrl-c
2021-03-22 RSim: symbol map, break, print, fix ALU simulation
2021-03-23 RSim: keyboard
2021-03-23 RSim: rendering VGA to PNG
2021-03-24 RSim: server
2021-03-24 RSim: variable server port
2021-03-24 RSim: PS/2 support
2021-03-26 RSim: card read
2021-03-26 Card image script for mac
2021-03-26 RSim: some readme
2021-03-26 Editor WIP
2021-03-26 Editor: cursor
2021-03-27 Editor: insert characters
2021-04-24 RSim: delete breakpoint
2021-04-24 RSim: check breakpoints after execution
2021-04-25 Natrix: store line number info
2021-04-25 Linker: YAML map file, save source line info
2021-04-25 RSim: break/until on line number
2021-04-25 RSim: readline
2021-04-25 FAT: fix read when file size is divisible by cluster size
2021-04-25 Editor: delete
2021-04-25 Editor: save
2021-04-25 RSim: add missed keys
2021-04-25 Editor: home, end, page up, page down
2021-04-25 Fileshell: don't add redundant slashes when appending path
2021-04-26 Assembler: save first line number, not last
2021-04-26 FAT: fix file write when size is multiple of a cluster
2021-04-26 Editor: nicer colors
2021-04-27 Editor: update without screen flickering
2021-04-27 Pong: fix glitch
2021-04-27 Life: better key bindings
2021-05-13 Tetris: collision logic
2021-05-13 RSim: fix input
2021-05-13 Tetris: auto falling pieces
2021-05-13 Tetris: score, levels, app
2021-08-15 Mandelbrot: BCDF-based implementation
2021-08-15 Natrix: SAR long numbers
2021-08-15 Natrix: long signed compare
2021-08-16 Natrix: fix SAR long in place
2021-08-16 Mandelbrot: fixed point implementation
2021-11-07 Natrix: on recursion save frame before populating parameters
2021-11-09 Plot: WIP
2021-11-09 Plot: shunting-yard parsing
2021-11-10 Natrix: handle nested array/struct member access
2021-11-10 Plot: RPN evaluation
2021-11-10 Plot: actually plot
2021-11-10 Plot: step increment instead of translating coordinates
2021-11-20 RSim: update README
2021-11-23 Update waveforms according to errata
2021-12-01 Update copyright
2021-12-02 Stack: stack controller model and tests
2021-12-02 Stack: schematics
2021-12-03 Stack: values and footprints
2021-12-04 Stack: more values
2021-12-04 Stack: power nets
2021-12-05 Stack: board
2021-12-06 Stack: production files
2021-12-06 RSim: rename module
2021-12-06 RSim: fix terminating newlines
2021-12-06 RSim: stack emulation
2021-12-07 Stack test program
2021-12-07 Natrix: inner and outer function arguments labels
2021-12-07 Natrix: support hardware stack
2021-12-08 Natrix: properly align variables on stack
2021-12-08 Natrix: don't use soft stack if hard stack is used
2021-12-08 Natrix: partial unit tests with HW stack
2021-12-08 Remove define
2021-12-16 Stack: update simulator and test program to match hardware
2022-07-19 Matrix app
2022-07-27 Z80: testbench, ld
2022-07-29 Z80: standard instruction loading for all instruction formats
2022-07-29 Z80: store indirect
2022-07-30 Z80: two more LDs
2022-07-30 Z80: ld (imm16), a
2022-07-30 Z80: 8-bit arithmetic operations
2022-07-30 Z80: simple inc/dec
2022-07-30 Z80: indirect inc/dec
2022-07-30 Z80: 16-bit load immediate
2022-08-01 Z80: 16-bit load indirect
2022-08-01 Z80: 16-bit store indirect
2022-08-01 Z80: pop
2022-08-01 Z80: LD SP, rr
2022-08-02 Z80: 16-bit ADD
2022-08-03 Z80: 16-bit ADC
2022-08-03 Z80: 16-bit INC and DEC
2022-08-03 Z80: exchange registers instructions
2022-08-04 Z80: EX HL, (SP)
2022-08-05 Z80: set
2022-08-05 Z80: res
2022-08-05 Z80: jp
2022-08-05 Z80: jr
2022-08-06 Z80: DJNZ
2022-08-06 Z80: call
2022-08-06 Z80: ret
2022-08-06 rsim: fix NEG carry and overflow flags
2022-08-06 rsim: fix NEG carry
2022-08-06 Z80: RST instructions and AF arithmetics
2022-08-06 Z80: more memory for test program
2022-08-06 Z80: SLA
2022-08-06 Z80: SRA
2022-08-06 rsim: fix NEG carry (again)
2022-08-06 Z80: block operations
2022-08-07 Z80: build system and hello world
2022-08-07 rsim: make state display cleaner
2022-08-08 Z80: shift and rotate, sprintf works
2022-08-08 rsim: secret Z80 panel
2022-08-08 Z80: rr
2022-08-08 Z80: rla
2022-08-08 Z80: rra
2022-08-08 Z80: uncomment area _HOME
2022-09-04 Z80: matrix code rain in C
2022-09-04 Move 74xx models to a submodule
2023-08-26 rsim: support qword print
2023-09-18 Assembler: weak export support
2023-10-10 Add requirements.txt
2023-10-10 Linker: fix AR support
2023-10-12 Eth: partial receive model
2023-10-16 Eth: receiver model WIP
2023-10-17 Eth: test normal operation
2023-10-17 Eth: test frame filtering
2023-10-17 Eth: test buffer overrun
2023-10-17 Eth: test read while receive
2023-10-18 Eth: latched re-arm
2023-10-20 Eth: receiver schematic
2023-10-24 Eth: transmitter model
2023-10-25 Eth: transmitter schematics finished
2023-10-29 Eth: schematics checked
2023-10-29 Eth: board dimensions
2023-11-01 Eth: board
2023-11-02 Eth: another transmitter test
2023-11-02 Eth: production files
2023-11-16 Eth: doc and errata
2023-11-25 rsim: VGA window
2023-11-25 rsim: apply rustfmt
2023-11-25 rsim: automatically deduce map file name
2023-11-26 linker: bloat segments
2023-12-18 font: more funny characters
2023-12-18 Linker: library path option
2023-12-18 rsim: allow decimal addresses for breakpoints etc
